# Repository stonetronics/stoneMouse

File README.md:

Stonetronics StoneMouse

A vusb-based mouse using a joystick and some buttons

This repository contains
- EAGLE - schematic, board and library
- Source code and atmel studio project

The StoneMouse uses an ATmega8-Controller running at 12 MHz for vusb.
It collects data from an potentiometer joystick and calculates deltax and deltay of the mousecursor. There was the issue that when releasing the Joystick, the adc values of the potis didnt snap back to preciese center values. To fix this an iir filter was implemented in an interval around the center position to determine mean center position and stop the cursor from drifting

These buttons have been implemented:
- left mouse button
- right mouse button
- scroll up
- scroll down
- change precision

The pcb was designed to fit mostly through hole components mounted in an smd-like way, so that there are no spiky through hole junctions on the backside of the pcb.
This was done primaryly to prevent the user from being stung by a through hole junction and because i had only through hole parts lying around
USB-connection is done by an Mini-USB connector

Build summary:
The StoneMouse pcb was etched with natriumpersulfate and the components were soldered. The controller was flashed before it was soldered on the pcb.
For the Joystick, there was a prototyping pcb soldered 90° to the top of the base pcb to hold the components. Several buttons were soldered onto a prototyping pcb which was soldered to the base pcb and the joystick pcb. All buttons are debumped by an 100nF smd capacitor. The mechanical structure was strengthened by pieces of raw pcb soldered to the other pcbs, forming a housing for the electronics.

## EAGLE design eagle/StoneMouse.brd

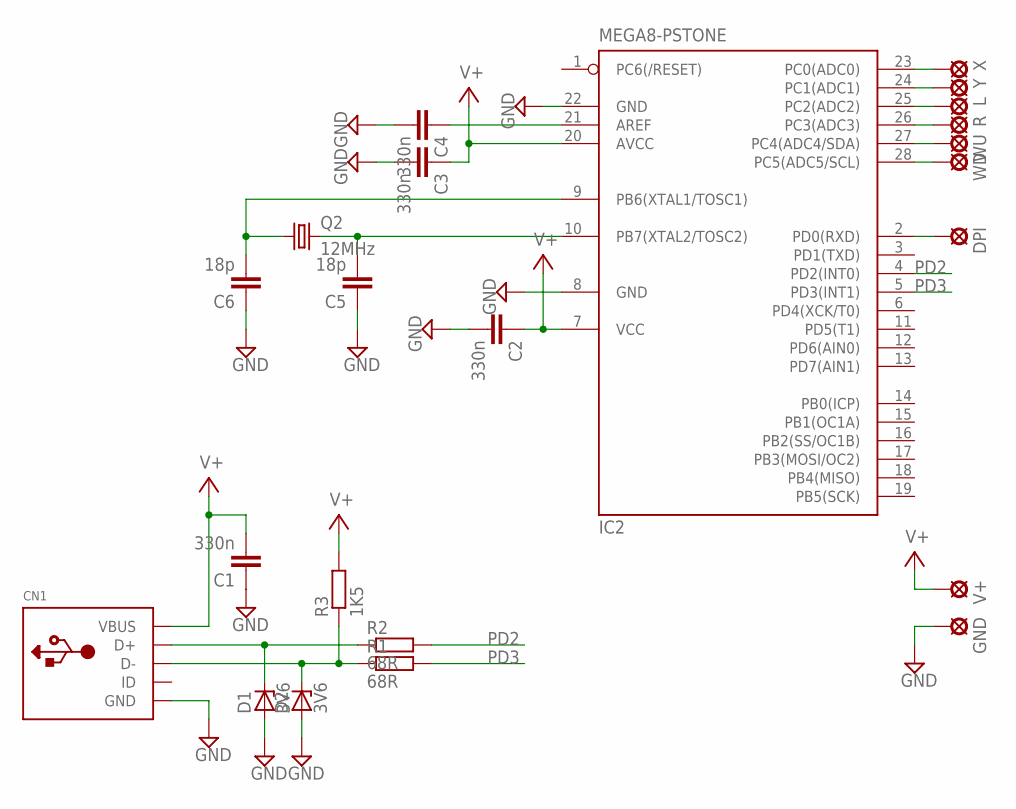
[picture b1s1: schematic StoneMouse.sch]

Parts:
C1, C2, C3, C4: 330n; 3X7_STONESMD
C5, C6: 18p; 3X7_STONESMD
CN1: USBMINIB; USB-MINIB
D1, D2: 3V6; DO35-7_STONESMD
DPI: SMD3X6
GND: SMD3X6
IC2: MEGA8-PSTONE; DIL28-3_STONESMD
L: SMD3X6
Q2: 12MHz; SM49
R: SMD3X6
R1, R2: 68R; 0204/7_STONESMD
R3: 1K5; 0204/7_STONESMD
V+: SMD3X6
WD: SMD3X6
WU: SMD3X6
X: SMD3X6
Y: SMD3X6

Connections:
GND: C1.P$1 (1), C2.P$2 (2), C3.P$2 (2), C4.P$2 (2), C5.P$1 (1), C6.P$1 (1), CN1.GND, D1.A, D2.A, GND.P$1, IC2.8 (GND), IC2.22 (GND)
unnamed: CN1.D+, D1.K (C), R2.P$1 (1)
unnamed: CN1.D-, D2.K (C), R1.P$1 (1), R3.P$1 (1)
unnamed: C4.P$1 (1), IC2.21 (AREF)
unnamed: DPI.P$1, IC2.2 (PD0(RXD))
unnamed: C6.P$2 (2), IC2.9 (PB6(XTAL1/TOSC1)), Q2.1
unnamed: C5.P$2 (2), IC2.10 (PB7(XTAL2/TOSC2)), Q2.2
unnamed: IC2.24 (PC1(ADC1)), Y.P$1
unnamed: IC2.23 (PC0(ADC0)), X.P$1
unnamed: IC2.25 (PC2(ADC2)), L.P$1
unnamed: IC2.26 (PC3(ADC3)), R.P$1
unnamed: IC2.27 (PC4(ADC4/SDA)), WU.P$1
unnamed: IC2.28 (PC5(ADC5/SCL)), WD.P$1
PD2: IC2.4 (PD2(INT0)), R2.P$2 (2)
PD3: IC2.5 (PD3(INT1)), R1.P$2 (2)
V+: C1.P$2 (2), C2.P$1 (1), C3.P$1 (1), CN1.VBUS, IC2.7 (VCC), IC2.20 (AVCC), R3.P$2 (2), V+.P$1

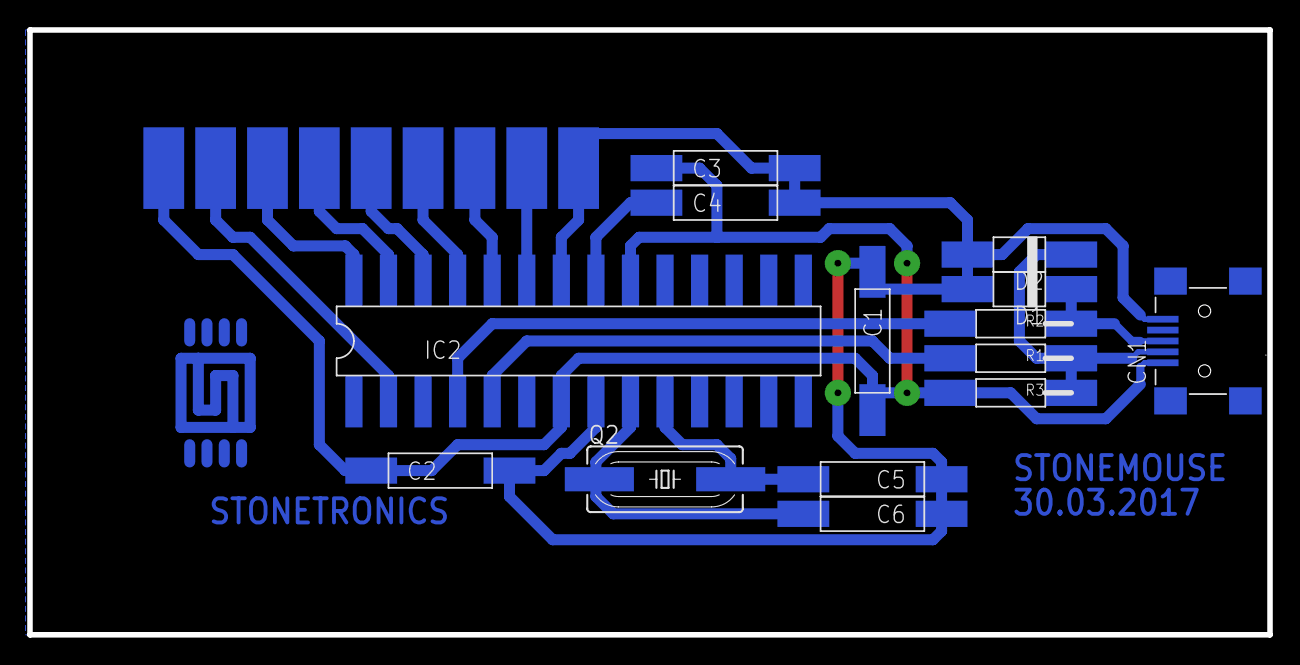
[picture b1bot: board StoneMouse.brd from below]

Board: 2 copper layers, 91.1 x 44.4 mm, 23 parts (14 on the bottom side), 16 nets.

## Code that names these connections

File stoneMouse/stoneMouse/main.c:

/* Name: main.c
 * Project: Joystick Mouse (from HID-Mouse Example by Christian Starkjohann)
 * Author: stonetronics
 * Creation Date: 2017.04.18
 * Copyright: (c) 2008 by OBJECTIVE DEVELOPMENT Software GmbH
 * License: GNU GPL v2 (see License.txt), GNU GPL v3 or proprietary (CommercialLicense.txt)
 */

/*
We use VID/PID 0x046D/0xC00E which is taken from a Logitech mouse. Don't
publish any hardware using these IDs! This is for demonstration only!
*/

#define DDR_BUTTONS		DDRC
#define PORT_BUTTONS	PORTC
#define PIN_BUTTONS		PINC
#define ANALOG_X		PC0
#define ANALOG_Y		PC1
#define BUTTON_LMB		PC2
#define BUTTON_RMB		PC3
#define BUTTON_WHEELUP	PC4
#define BUTTON_WHEELDWN	PC5
#define DDR_DPI			DDRD
#define PORT_DPI		PORTD
#define PIN_DPI			PIND
#define BUTTON_DPI		PD0



#define AVG_SIZE	8
#define NORM_THRESHOLD	15
#define F_CPU			12000000

#include <avr/io.h>
#include <avr/wdt.h>
#include <avr/interrupt.h>  /* for sei() */
#include <util/delay.h>     /* for _delay_ms() */

#include <avr/pgmspace.h>   /* required by usbdrv.h */
#include "usbdrv/usbdrv.h"

#include "adc.h" // for adc functions, obviously
//#include "uart.h" // for uart debugging

/* ------------------------------------------------------------------------- */
/* ----------------------------- USB interface ----------------------------- */
/* ------------------------------------------------------------------------- */

PROGMEM const char usbHidReportDescriptor[52] = { /* USB report descriptor, size must match usbconfig.h */
    0x05, 0x01,                    // USAGE_PAGE (Generic Desktop)
    0x09, 0x02,                    // USAGE (Mouse)
    0xa1, 0x01,                    // COLLECTION (Application)
    0x09, 0x01,                    //   USAGE (Pointer)
    0xA1, 0x00,                    //   COLLECTION (Physical)
    0x05, 0x09,                    //     USAGE_PAGE (Button)
    0x19, 0x01,                    //     USAGE_MINIMUM
    0x29, 0x03,                    //     USAGE_MAXIMUM
    0x15, 0x00,                    //     LOGICAL_MINIMUM (0)
    0x25, 0x01,                    //     LOGICAL_MAXIMUM (1)
    0x95, 0x03,                    //     REPORT_COUNT (3)
    0x75, 0x01,                    //     REPORT_SIZE (1)
    0x81, 0x02,                    //     INPUT (Data,Var,Abs)
    0x95, 0x01,                    //     REPORT_COUNT (1)
    0x75, 0x05,                    //     REPORT_SIZE (5)
    0x81, 0x03,                    //     INPUT (Const,Var,Abs)
    0x05, 0x01,                    //     USAGE_PAGE (Generic Desktop)
    0x09, 0x30,                    //     USAGE (X)
    0x09, 0x31,                    //     USAGE (Y)
    0x09, 0x38,                    //     USAGE (Wheel)
    0x15, 0x81,                    //     LOGICAL_MINIMUM (-127)
    0x25, 0x7F,                    //     LOGICAL_MAXIMUM (127)
    0x75, 0x08,                    //     REPORT_SIZE (8)
    0x95, 0x03,                    //     REPORT_COUNT (3)
    0x81, 0x06,                    //     INPUT (Data,Var,Rel)
    0xC0,                          //   END_COLLECTION
    0xC0,                          // END COLLECTION
};
/* This is the same report descriptor as seen in a Logitech mouse. The data
 * described by this descriptor consists of 4 bytes:
 *      .  .  .  .  . B2 B1 B0 .... one byte with mouse button states
 *     X7 X6 X5 X4 X3 X2 X1 X0 .... 8 bit signed relative coordinate x
 *     Y7 Y6 Y5 Y4 Y3 Y2 Y1 Y0 .... 8 bit signed relative coordinate y
 *     W7 W6 W5 W4 W3 W2 W1 W0 .... 8 bit signed relative coordinate wheel
 */
typedef struct{
    uchar   buttonMask;
    char    dx;
    char    dy;
    char    dWheel;
}report_t;

void normXY(uint8_t x, uint8_t y, int8_t* x_norm, int8_t* y_norm);

static report_t reportBuffer;
static uchar    idleRate;   /* repeat rate for keyboards, never used for mice */

/* ------------------------------------------------------------------------- */

usbMsgLen_t usbFunctionSetup(uchar data[8])
{
usbRequest_t    *rq = (void *)data;

    /* The following requests are never used. But since they are required by
     * the specification, we implement them in this example.
     */
    if((rq->bmRequestType & USBRQ_TYPE_MASK) == USBRQ_TYPE_CLASS){    /* class request type */
        if(rq->bRequest == USBRQ_HID_GET_REPORT){  /* wValue: ReportType (highbyte), ReportID (lowbyte) */
            /* we only have one report type, so don't look at wValue */
            usbMsgPtr = (void *)&reportBuffer;
            return sizeof(reportBuffer);
        }else if(rq->bRequest == USBRQ_HID_GET_IDLE){
            usbMsgPtr = &idleRate;
            return 1;
        }else if(rq->bRequest == USBRQ_HID_SET_IDLE){
            idleRate = rq->wValue.bytes[1];
        }
    }else{
        /* no vendor specific requests implemented */
    }
    return 0;   /* default for not implemented requests: return no data back to host */
}

/* ------------------------------------------------------------------------- */

int __attribute__((noreturn)) main(void)
{
	uchar   i;
	uint8_t x_raw;
	uint8_t y_raw;
	int8_t x_norm;
	int8_t y_norm;
	uint8_t dpi_factor = 2;

	uint8_t button_lmb;
	uint8_t button_rmb;
	uint8_t button_wheelup;
	uint8_t button_wheeldwn;
	uint8_t button_dpi;
	uint8_t button_dpi_old;

	/* init button ports & stuff */
	//set all buttons and analog inputs to input
	DDR_BUTTONS &= ~((1<<ANALOG_X) | (1<<ANALOG_Y) | (1<<BUTTON_LMB) | (1<<BUTTON_RMB) | (1<<BUTTON_WHEELUP) | (1<<BUTTON_WHEELDWN));
	DDR_DPI &= ~(1<<BUTTON_DPI);
	//set pullups on all buttons
	PORT_BUTTONS |= (1<<BUTTON_LMB) | (1<<BUTTON_RMB) | (1<<BUTTON_WHEELUP) | (1<<BUTTON_WHEELDWN);
	PORT_DPI |= (1<<BUTTON_DPI);
	button_dpi_old = PIN_DPI & (1<<BUTTON_DPI);

	adc_init();
	//uart_init();
    wdt_enable(WDTO_1S); //needed
    usbInit();
    usbDeviceDisconnect();  /* enforce re-enumeration, do this while interrupts are disabled! */
    i = 0;
    while(--i){             /* fake USB disconnect for > 250 ms */
        wdt_reset();
        _delay_ms(1);
    }

    usbDeviceConnect();
    sei();
    while(1){                /* main event loop */
        wdt_reset();
        usbPoll();
		if(usbInterruptIsReady()){
            /* called after every poll of the interrupt endpoint */
            usbSetInterrupt((void *)&reportBuffer, sizeof(reportBuffer));
        }

		/*button inputs handling*/
		//scan all buttons
		button_rmb = PIN_BUTTONS & (1<<BUTTON_RMB);
		button_lmb = PIN_BUTTONS & (1<<BUTTON_LMB);
		button_wheelup = PIN_BUTTONS & (1<<BUTTON_WHEELUP);
		button_wheeldwn = PIN_BUTTONS & (1<<BUTTON_WHEELDWN);
		button_dpi = PIN_DPI & (1<<BUTTON_DPI);

		if(!button_lmb)
			reportBuffer.buttonMask |= (1<<0); //activate left mousebutton
		else
			reportBuffer.buttonMask &= ~(1<<0); //deactivate left mousebutton

		if(!button_rmb)
			reportBuffer.buttonMask |= (1<<1); //activate right mousebutton
		else
			reportBuffer.buttonMask &= ~(1<<1); //deactivate right mousebutton
		
		//button emulated mousewheel
		if(!button_wheelup)
			reportBuffer.dWheel = 10/dpi_factor;
		else if(!button_wheeldwn)
			reportBuffer.dWheel = -10/dpi_factor;
		else
			reportBuffer.dWheel = 0;

		//if dpi button pressed switch through various dpi factors
		if(button_dpi != button_dpi_old)
		{
			button_dpi_old = button_dpi;
			if(!button_dpi)
			{
				switch(dpi_factor)
				{
					case 1:
						dpi_factor = 2;
						break;
					case 2:
						dpi_factor = 5;
						break;
					case 5:
						dpi_factor = 10;
						break;
					case 10:
						dpi_factor = 1;
						break;
					default:
						dpi_factor = 2;
						break;
				}
			}
		}
		
		//joystick input stuff
		if(adc_updateValues(&(x_raw), &(y_raw)))
		{	
			normXY(x_raw, y_raw, &x_norm, &y_norm );
			reportBuffer.dx = x_norm/dpi_factor;
			reportBuffer.dy = y_norm/dpi_factor;
		}

    }
}


void normXY(uint8_t x, uint8_t y, int8_t* x_norm, int8_t* y_norm)
{
	static uint8_t firstrun = 1;
	static float x_avg = 128;
	static uint8_t x_upperThreshold = 130;
	static uint8_t x_lowerThreshold = 120;
	static float y_avg = 128;
	static uint8_t y_upperThreshold = 130;
	static uint8_t y_lowerThreshold = 120;

	if(firstrun)
	{
		x_avg = (float)x;
		x_upperThreshold = x_avg + NORM_THRESHOLD;
		x_lowerThreshold = x_avg - NORM_THRESHOLD;
		y_avg = (float)y;
		y_upperThreshold = y_avg + NORM_THRESHOLD;
		y_lowerThreshold = y_avg - NORM_THRESHOLD;
		firstrun = 0;
	}

	if ((x > x_lowerThreshold) && (x < x_upperThreshold))
	{
		x_avg = x_avg * ((float)(AVG_SIZE - 1)/AVG_SIZE) + ((float)x) * 1/((float) AVG_SIZE);
	}

	if ((y > (y_lowerThreshold)) && (y < (y_upperThreshold)))
	{
		y_avg = y_avg * ((float)(AVG_SIZE - 1)/AVG_SIZE) + ((float)y) * 1/((float) AVG_SIZE);
	}

	*x_norm =(int8_t)( ((float) x) - x_avg );
	*y_norm =(int8_t)( y_avg - ((float) y) );
}
/* ------------------------------------------------------------------------- */
